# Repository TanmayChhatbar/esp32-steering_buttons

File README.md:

# ESP32 Steering Buttons

## What you will need

- A steering wheel
- A few buttons
- A few encoders
- ESP32-S3 Supermini
- Simagic QR70 Quick-release (I use this for powering the ESP32 on the board)

## Notes

This repository is more a demo than a guide for DIY wheel buttons for an ESP32.

It uses the lemmingdev/ESP32-BLE-Gamepad library to handle the joystick control component.

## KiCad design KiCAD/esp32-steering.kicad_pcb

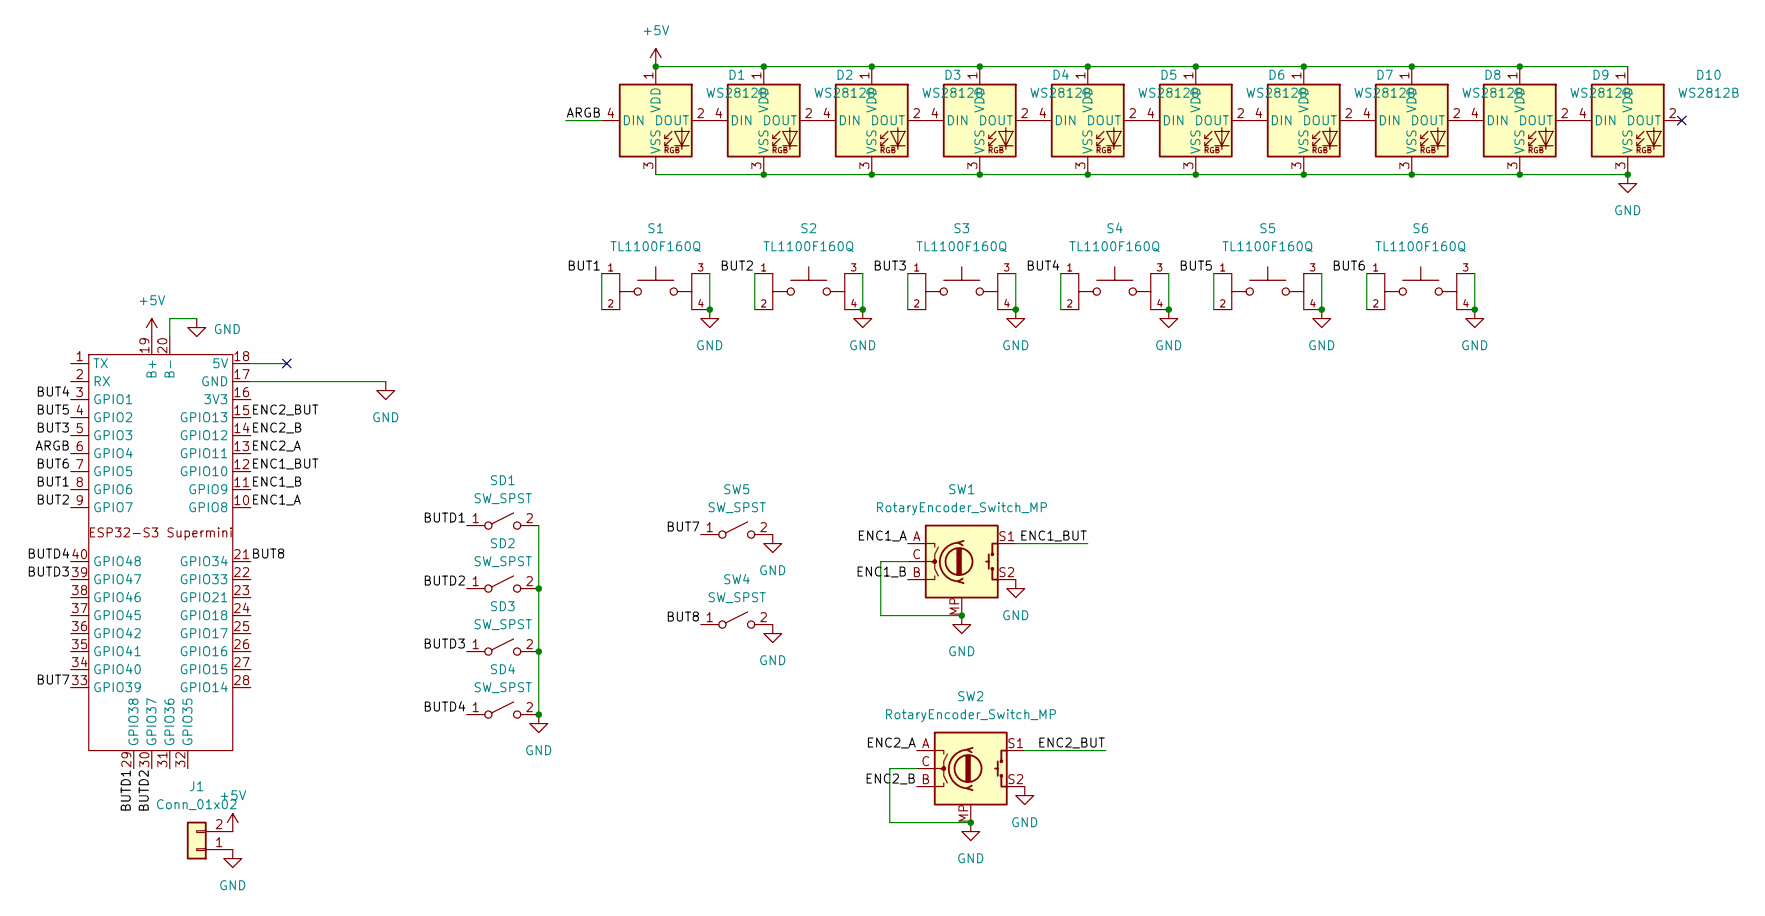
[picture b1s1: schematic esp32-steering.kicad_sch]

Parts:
D1, D2, D3, D4, D5, D6, D7, D8, D9, D10: WS2812B; LED_WS2812B_PLCC4_5.0x5.0mm_P3.2mm
J1: Conn_01x02; JST_XH_S2B-XH-A-1_1x02_P2.50mm_Horizontal-short
S1, S2, S3, S4, S5, S6: TL1100F160Q; SW_TL1100F160Q; PARTREV D
SD1, SD2, SD3, SD4: SW_SPST; SW_Push_SPST_NO_Alps_SKRK
SW1, SW2: RotaryEncoder_Switch_MP; RotaryEncoder_Alps_EC11E-Switch_Vertical_H20mm_MountingHoles
SW4, SW5: SW_SPST; SW_D2FC_OMR
U1: ESP32-S3 Supermini

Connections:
+5V: D1.1 (VDD), D2.1 (VDD), D3.1 (VDD), D4.1 (VDD), D5.1 (VDD), D6.1 (VDD), D7.1 (VDD), D8.1 (VDD), D9.1 (VDD), D10.1 (VDD), J1.2, U1.19 (B+)
/ARGB: D1.4 (DIN), U1.6 (GPIO4)
/BUT1: S1.1, S1.2, U1.8 (GPIO6)
/BUT2: S2.1, S2.2, U1.9 (GPIO7)
/BUT3: S3.1, S3.2, U1.5 (GPIO3)
/BUT4: S4.1, S4.2, U1.3 (GPIO1)
/BUT5: S5.1, S5.2, U1.4 (GPIO2)
/BUT6: S6.1, S6.2, U1.7 (GPIO5)
/BUT7: SW5.1 (A), U1.33 (GPIO39)
/BUT8: SW4.1 (A), U1.21 (GPIO34)
/BUTD1: SD1.1 (A), U1.29 (GPIO38)
/BUTD2: SD2.1 (A), U1.30 (GPIO37)
/BUTD3: SD3.1 (A), U1.39 (GPIO47)
/BUTD4: SD4.1 (A), U1.40 (GPIO48)
/ENC1_A: SW1.A, U1.10 (GPIO8)
/ENC1_B: SW1.B, U1.11 (GPIO9)
/ENC1_BUT: SW1.S1, U1.12 (GPIO10)
/ENC2_A: SW2.A, U1.13 (GPIO11)
/ENC2_B: SW2.B, U1.14 (GPIO12)
/ENC2_BUT: SW2.S1, U1.15 (GPIO13)
GND: D1.3 (VSS), D2.3 (VSS), D3.3 (VSS), D4.3 (VSS), D5.3 (VSS), D6.3 (VSS), D7.3 (VSS), D8.3 (VSS), D9.3 (VSS), D10.3 (VSS), J1.1, S1.3, S1.4, S2.3, S2.4, S3.3, S3.4, S4.3, S4.4, S5.3, S5.4, S6.3, S6.4, SD1.2 (B), SD2.2 (B), SD3.2 (B), SD4.2 (B), SW1.C, SW1.MP, SW1.S2, SW2.C, SW2.MP, SW2.S2, SW4.2 (B), SW5.2 (B), U1.17 (GND), U1.20 (B-)
unnamed: D1.2 (DOUT), D2.4 (DIN)
unnamed: D2.2 (DOUT), D3.4 (DIN)
unnamed: D3.2 (DOUT), D4.4 (DIN)
unnamed: D4.2 (DOUT), D5.4 (DIN)
unnamed: D5.2 (DOUT), D6.4 (DIN)
unnamed: D6.2 (DOUT), D7.4 (DIN)
unnamed: D7.2 (DOUT), D8.4 (DIN)
unnamed: D8.2 (DOUT), D9.4 (DIN)
unnamed: D9.2 (DOUT), D10.4 (DIN)

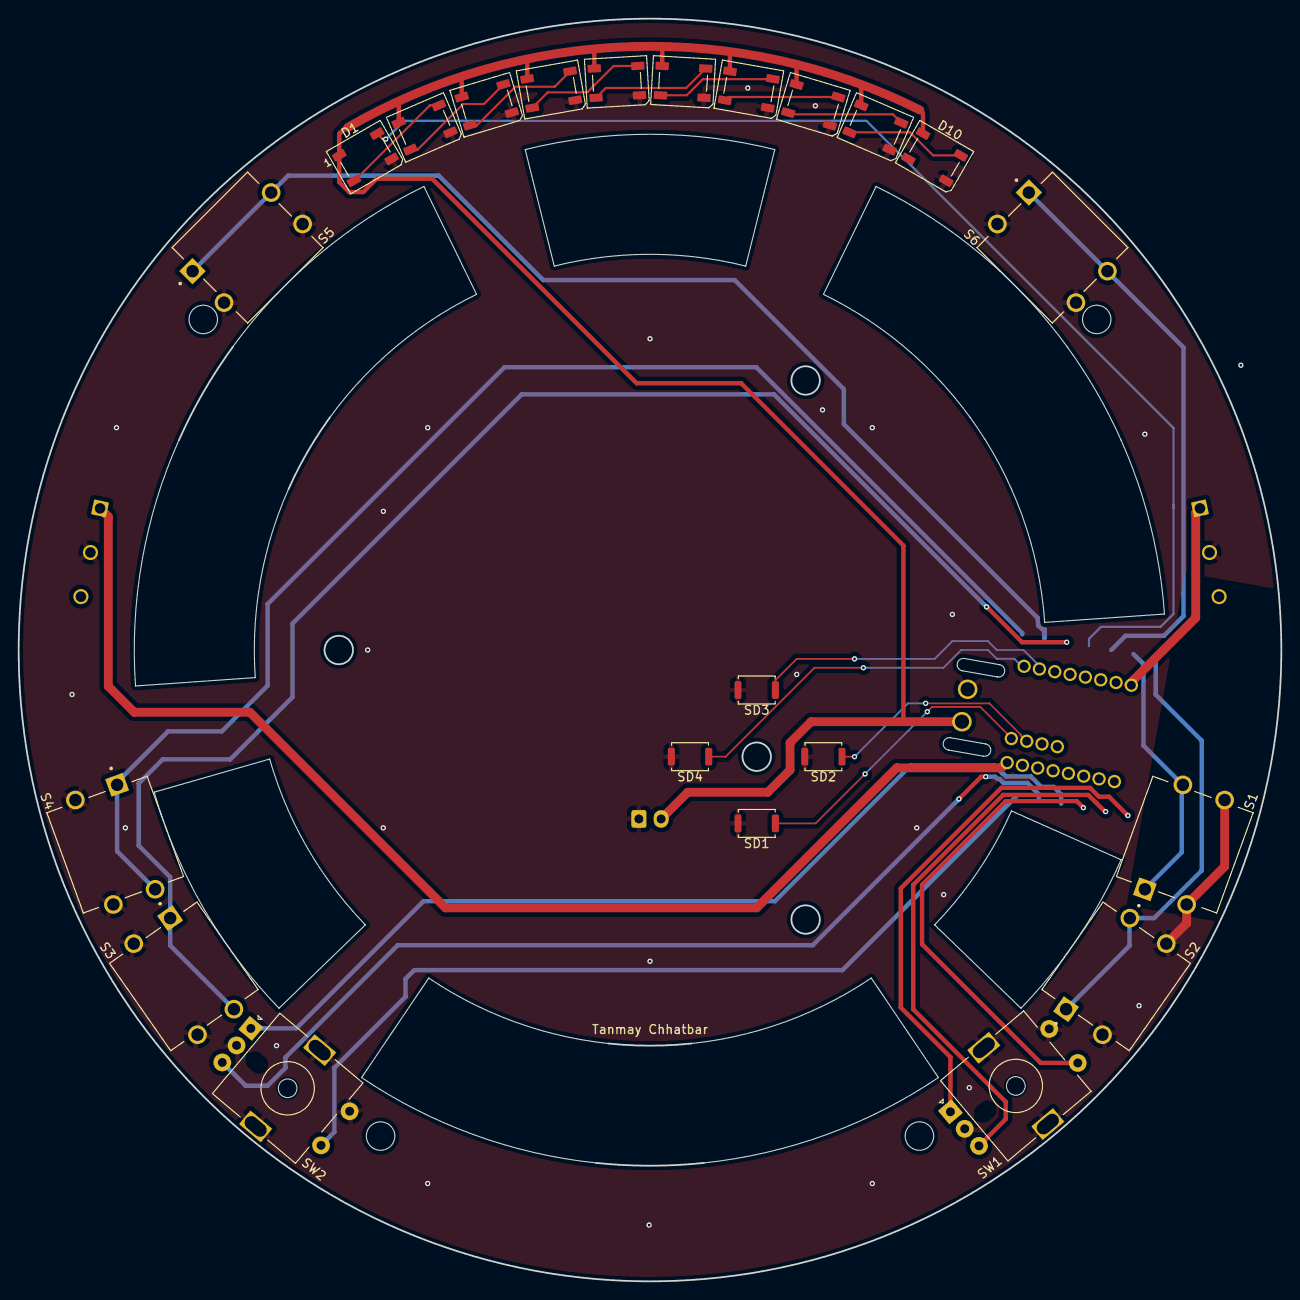
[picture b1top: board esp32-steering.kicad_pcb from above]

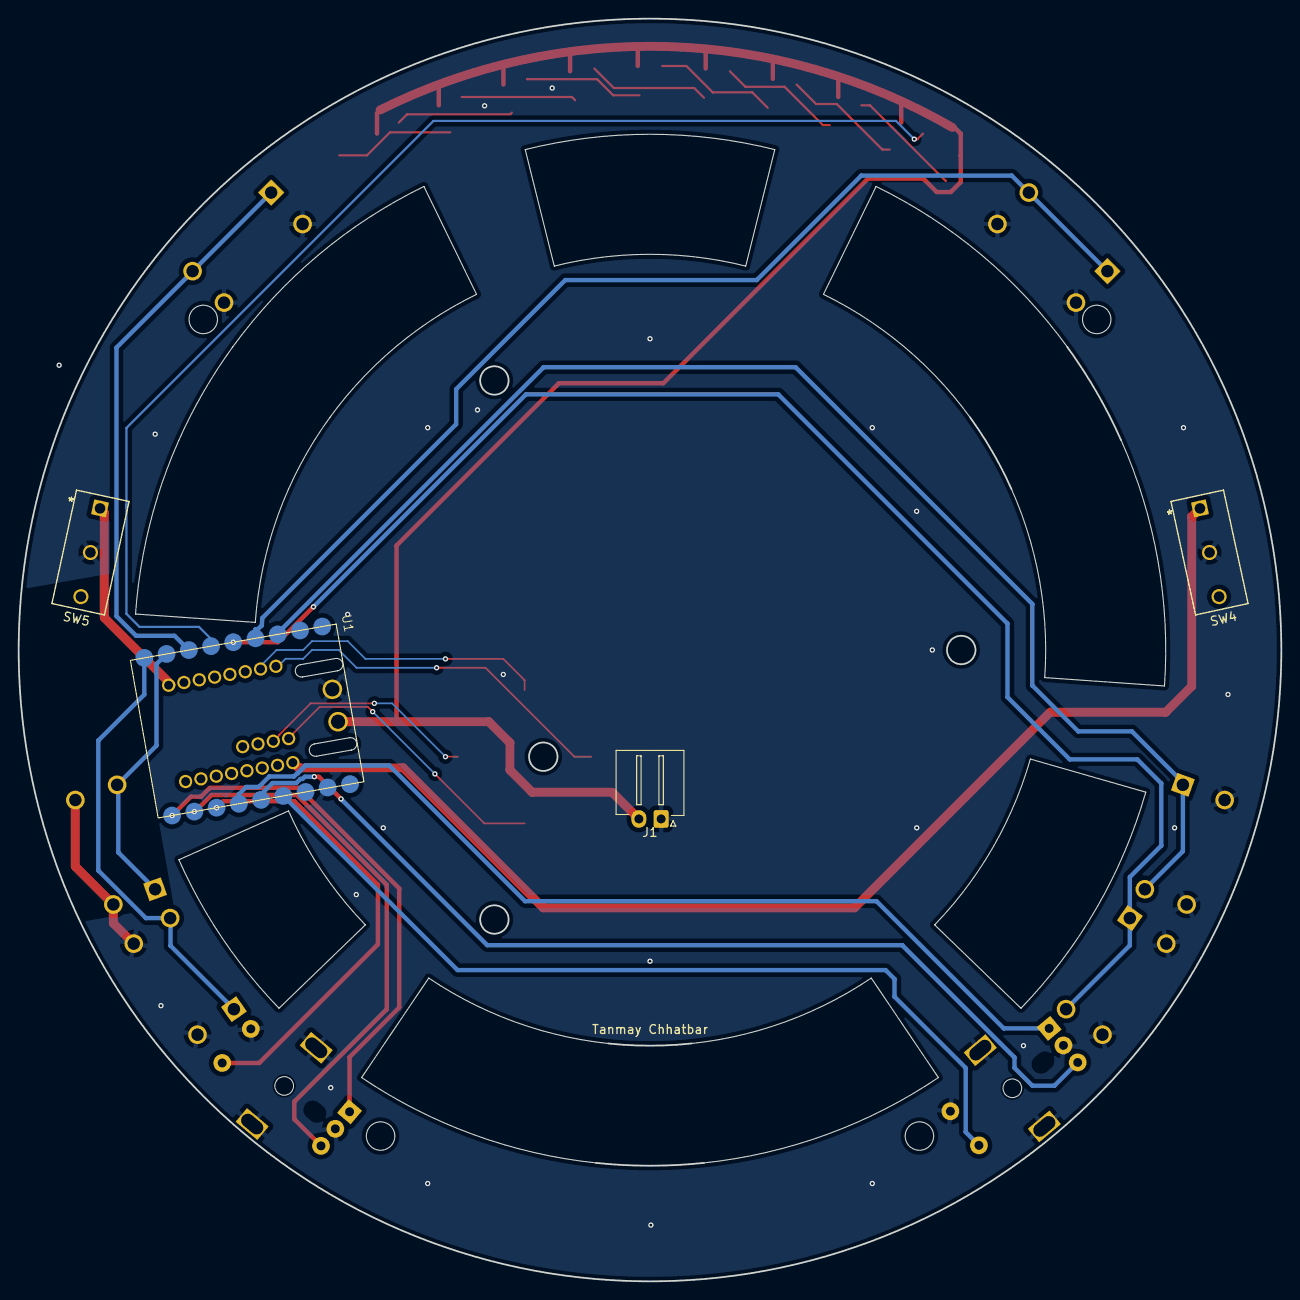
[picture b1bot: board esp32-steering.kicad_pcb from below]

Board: 2 copper layers, 142.0 x 142.0 mm, 26 parts (4 on the bottom side), 30 nets.

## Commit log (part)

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2026-02-04 kicad files - export version
2026-02-04 code init
2026-02-17 correct footprint and pcb design for battery connections
2026-02-17 basic button test works
2026-02-18 gamepad works
2026-02-18 shift encoder buttons to prevent clash
2026-02-22 code refactor
2026-02-22 OTA update
2026-02-28 add CAD, mp4 and readme
2026-02-28 modify readme, trying to get video to work
2026-02-28 retry transparent image
